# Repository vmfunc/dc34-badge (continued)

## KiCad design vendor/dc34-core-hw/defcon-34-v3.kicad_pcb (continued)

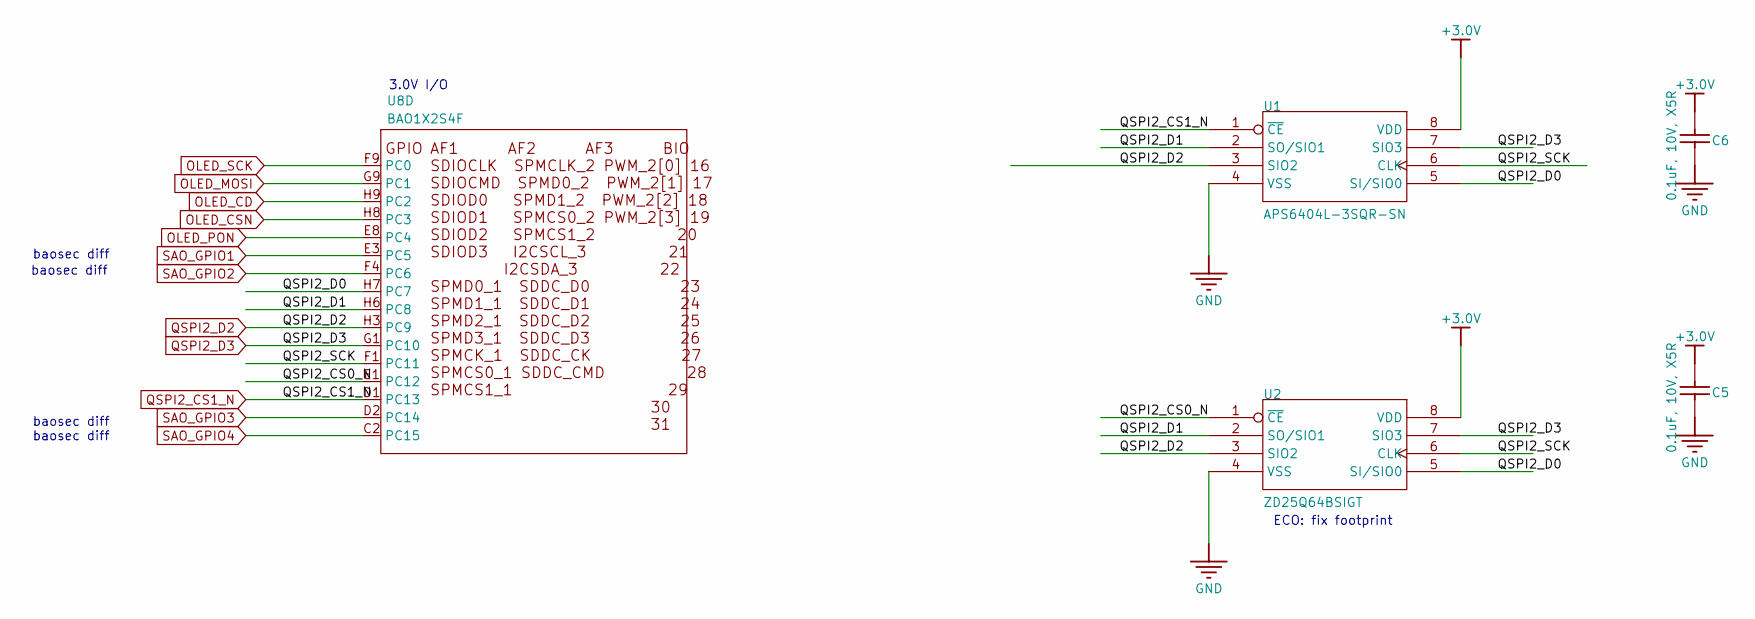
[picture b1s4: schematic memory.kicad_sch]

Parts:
C5, C6: 0.1uF, 10V, X5R; C_0201_0603Metric; MPN CL05B104KO5NNNC; LCSC C76934
U1: APS6404L-3SQR-SN; SOIC-8_3.9x4.9mm_P1.27mm; MPN APS6404L-3SQR-SN; LCSC C5333729
U2: ZD25Q64BSIGT; SOIC-8_5.3x5.3mm_P1.27mm; LCSC C2687407
U8: BAO1X2S4F; WLCSP-71_9x8_4.062x3.762mm

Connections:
+3.0V: C5.1, C6.1, U1.8 (VDD), U2.8 (VDD); also elsewhere on the board
/memory/QSPI2_CS0_N: U2.1 (~CE), U8.E1 (PC12)
/memory/QSPI2_D0: U1.5 (SI/SIO0), U2.5 (SI/SIO0), U8.H7 (PC7)
/memory/QSPI2_D1: U1.2 (SO/SIO1), U2.2 (SO/SIO1), U8.H6 (PC8)
/memory/QSPI2_SCK: U1.6 (CLK), U2.6 (CLK), U8.F1 (PC11)
GND: C5.2, C6.2, U1.4 (VSS), U2.4 (VSS); also elsewhere on the board
OLED_CD: U8.H9 (PC2); also elsewhere on the board
OLED_CSN: U8.H8 (PC3); also elsewhere on the board
OLED_MOSI: U8.G9 (PC1); also elsewhere on the board
OLED_PON: U8.E8 (PC4); also elsewhere on the board
OLED_SCK: U8.F9 (PC0); also elsewhere on the board
QSPI2_CS1_N: U1.1 (~CE), U8.D1 (PC13)
QSPI2_D2: U1.3 (SIO2), U2.3 (SIO2), U8.H3 (PC9)
QSPI2_D3: U1.7 (SIO3), U2.7 (SIO3), U8.G1 (PC10)
SAO_GPIO1: U8.E3 (PC5); also elsewhere on the board
SAO_GPIO2: U8.F4 (PC6); also elsewhere on the board
SAO_GPIO3: U8.D2 (PC14); also elsewhere on the board
SAO_GPIO4: U8.C2 (PC15); also elsewhere on the board

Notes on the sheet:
baosec diff
ECO: fix footprint
3.0V I/O

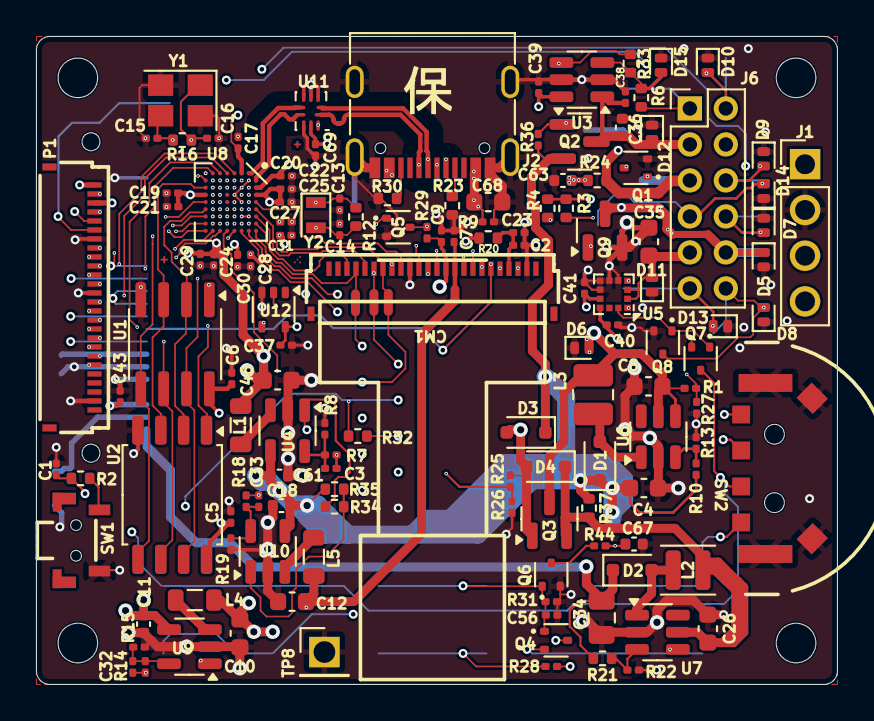
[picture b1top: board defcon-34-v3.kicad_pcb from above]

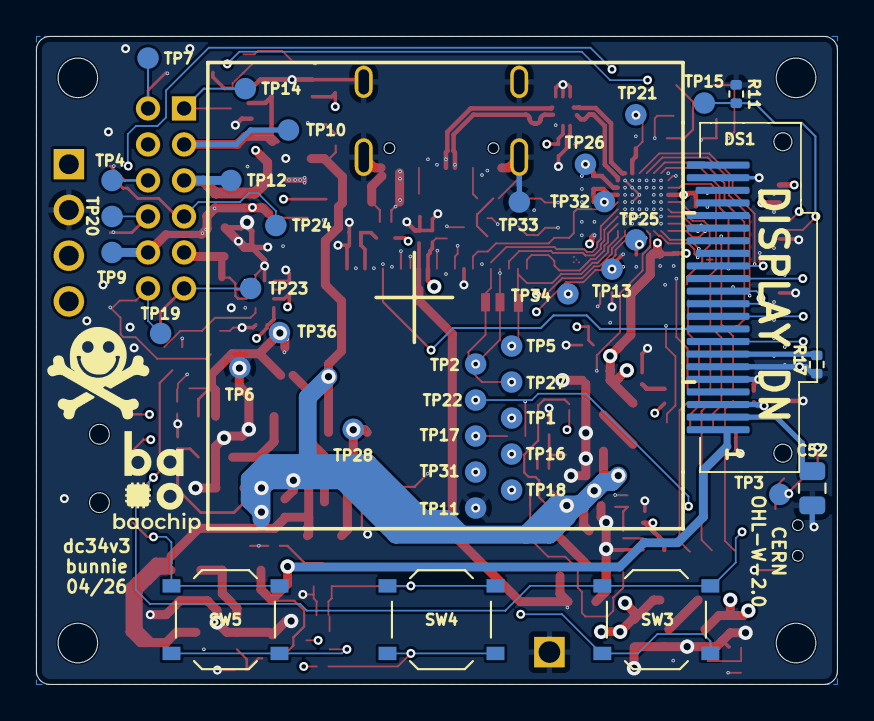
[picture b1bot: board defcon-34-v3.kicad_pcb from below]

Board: 6 copper layers, 44.5 x 36.0 mm, 185 parts (38 on the bottom side), 101 nets.
